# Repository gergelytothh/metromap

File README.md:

# Metromap

A map of the Budapest metro, designed to show trains moving on all four lines. There are 96 LEDs on the map: two at each station (one per direction) and one at each terminus. They are hand-wired and soldered onto the map and driven by an ESP32 through a custom PCB. Right now it runs a simulated train animation; live data from BKK is the next step.

I'd seen lit-up metro maps of other cities online, but none of Budapest, and I didn't like the design of the ones I found. Since I'm studying electrical engineering anyway, I decided to build my own.

## How it works

The LEDs are driven by two MAX7219 chips, controlled by an ESP32. Each chip has 16 outputs: 8 DIG (digit) pins that sink current and 8 SEG (segment) pins that source it. Each LED sits where one DIG line and one SEG line cross, so one chip can control 64 LEDs and the two together 128.

Only one DIG line is active at a time. The chip sets the SEG lines for the LEDs that should be lit in that row, pulls the DIG line low, then moves on to the next row. It cycles through all 8 rows hundreds of times a second, so every lit LED looks constantly on.

The two chips are daisy-chained: they share the ESP32's clock and load pins, and U1's data output feeds U2's data input. The ESP32 shifts out 32 bits, a 16-bit word for each chip (an 8-bit register address and 8 bits of data, which set the SEG lines for one DIG row), and then a pulse on LOAD makes both chips apply them at the same time.

There are 96 LEDs, so one chip wasn't enough. I split them by metro line, so each line stays on a single chip and both chips stay under the 64-LED limit:

| Chip | Lines | LEDs used | Spare slots |
|---|---|---|---|
| U1 | M1 + M2 | 40 | 24 |
| U2 | M3 + M4 | 56 | 8 |

Every LED has an ID (1–96) and is assigned a chip, a DIG and a SEG. This mapping table is in [station_map.h](firmware/metromap/station_map.h) (also as [a CSV](hardware/led-mapping.csv)).

The firmware builds on this table:

- **One LED by ID**: looks the ID up in the table and turns on that chip/DIG/SEG.
- **Walk test**: lights every LED in turn, 1 to 96, and prints its station to the Serial Monitor, so wiring mistakes are easy to spot.
- **Train mode**: each line gets a route, from one terminus out along the forward LEDs and back along the backward ones, and four trains, one per line, move one stop at a time.

## Hardware

I designed the driver PCB myself in KiCAD and had it made by NYÁKÁRUHÁZ Kft. It holds both MAX7219s in DIP sockets, so the soldering heat couldn't damage the chips. Every DIG and SEG pin goes to a labelled pad.

From each pad, a wire runs to the back of the map, where it connects to the right LEDs. That's around ~280 solder joints in total, all by hand.

*The back of the map. Every wire is labelled in pencil with its DIG/SEG line.*

| Part | What |
|---|---|
| Microcontroller | ESP32-WROOM-32U dev board |
| LED drivers | 2 × MAX7219 (DIP-24, socketed) |
| PCB | Own design in KiCAD, made by NYÁKÁRUHÁZ Kft. |
| LEDs | 96, one colour per line |
| Map | Printed poster on cardboard |
| Power | 5 V from USB, via the ESP32 |

Design files: [schematic (PDF)](hardware/Metromap%20schematic.pdf) · [KiCAD project](hardware/kicad/) · [3D render](docs/images/pcb-3d.png)

### What I'd do differently

- **The wiring.** It works, but it's hard to trace and service. Next time I'd group the LEDs on small boards or connectors behind each line, with ribbon cable to the driver board.
- **The ISET resistor.** Both chips share one 10 kΩ R1, but each MAX7219 should have its own. According to the datasheet’s output current curves, a shared resistor behaves roughly like 20 kΩ per chip, about 25 mA peak per segment instead of about 45 mA, and the split between the chips isn’t guaranteed to be even. It works and the brightness looks fine, but a second version would give each chip its own resistor.

## Build and flash

Built with Arduino IDE 2.3.10 and the Espressif ESP32 board package 3.3.12.

1. Install the **MD_MAX72xx** library (by majicDesigns, tested with 3.5.1) from the Library Manager.
2. Open `firmware/metromap/metromap.ino`.
3. Select **Tools → Board → ESP32 Dev Module** and the ESP32's serial port.
4. Upload.

Pick the mode in `loop()`: `trainMode()` runs the train animation, and `walkTest()` lights every LED in turn and prints each station to the Serial Monitor (115200 baud).

## What went wrong and how I fixed it

For a long time the addressing didn't work: telling the firmware to light a specific DIG/SEG lit the wrong LED. I lit one address at a time and wrote down which LED actually came on, until a pattern appeared: the MD_MAX72xx library numbers the columns in a different order from the chip's SEG pins. SEG_A is column 6, down to SEG_G at column 0, and only SEG_DP stays at column 7. I then tested that theory LED by LED, and it held. The fix is a single line in [metromap.ino](firmware/metromap/metromap.ino).

More in the [bring-up log](docs/bring-up-log.md), including how the datasheet corrected my assumption about the shared ISET resistor.

## What's next

- **Live trains.** I chose the ESP32 for its built-in Wi-Fi. The plan is to fetch data from BKK's open API using an API key. As it turns out, BKK doesn't publish live positions for metro trains, only a timetable that's updated in real time, so the map has to work out where each train is from that.
- **Turning a timetable into train positions.** This is the tricky part. Using the timetable directly, a train could disappear between two stations, or appear at several at once. Each train has to be tracked so that it's always shown at exactly one station: the last station it departed from, until its scheduled departure from the next one.

## Acknowledgements

The firmware and this README were developed in collaboration with Claude and Claude Code. The hardware design, PCB, wiring and testing are my own.

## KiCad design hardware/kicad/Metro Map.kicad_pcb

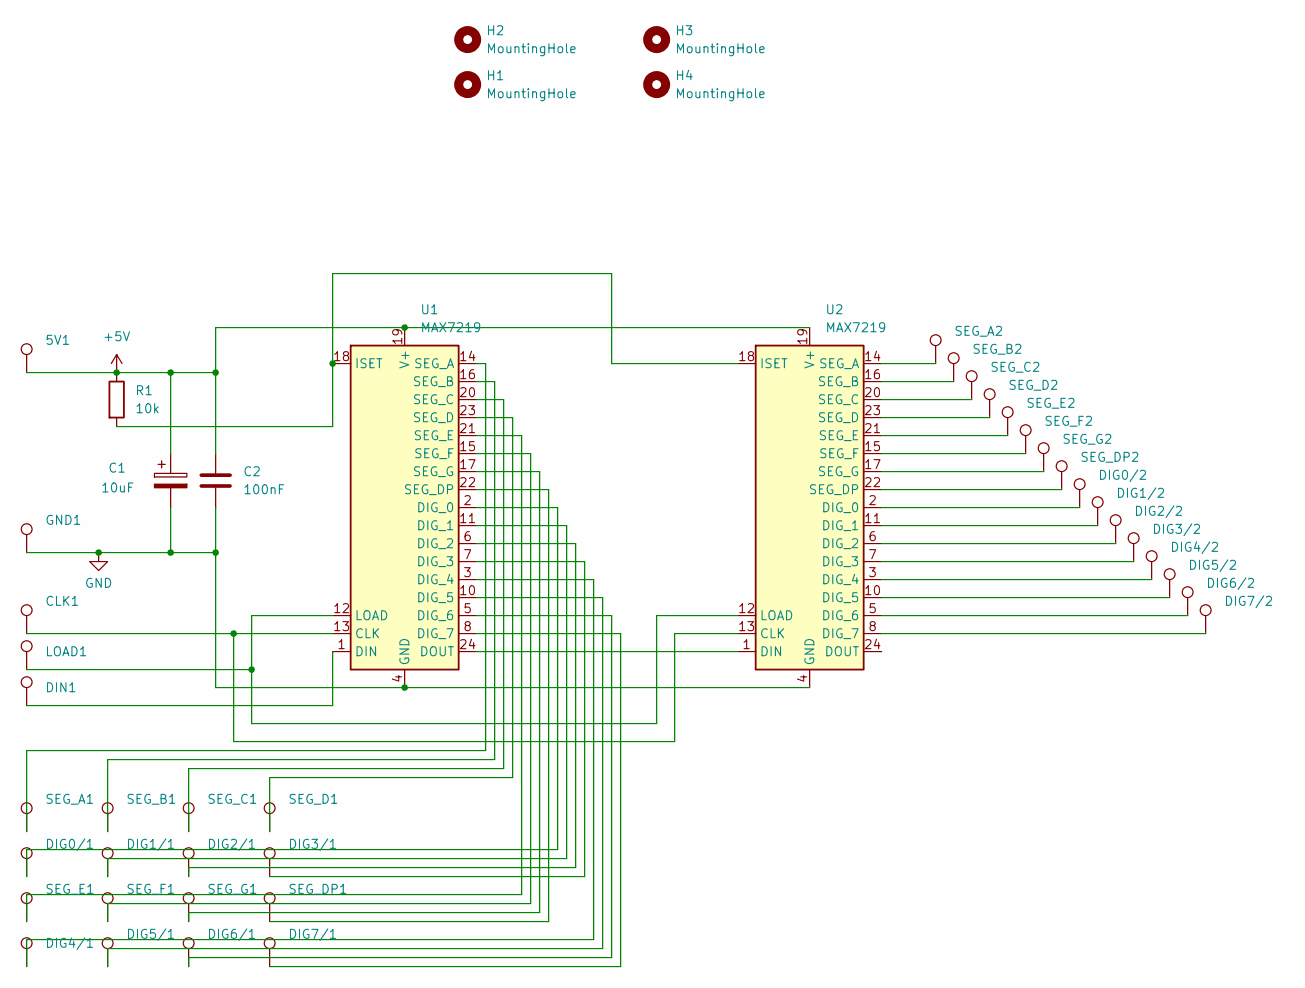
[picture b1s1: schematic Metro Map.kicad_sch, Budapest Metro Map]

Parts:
5V1: TestPoint_THTPad_D1.5mm_Drill0.7mm
C1: 10uF; CP_Radial_D5.0mm_P2.00mm
C2: 100nF; C_Disc_D5.0mm_W2.5mm_P2.50mm
CLK1: TestPoint_THTPad_D1.5mm_Drill0.7mm
DIG0/1, DIG0/2, DIG1/1, DIG1/2, DIG2/1, DIG2/2, DIG3/1, DIG3/2, DIG4/1, DIG4/2, DIG5/1, DIG5/2, DIG6/1, DIG6/2, DIG7/1, DIG7/2: TestPoint_THTPad_D1.5mm_Drill0.7mm
DIN1: TestPoint_THTPad_D1.5mm_Drill0.7mm
GND1: TestPoint_THTPad_D1.5mm_Drill0.7mm
H1, H2, H3, H4: MountingHole; MountingHole_3.2mm_M3
LOAD1: TestPoint_THTPad_D1.5mm_Drill0.7mm
R1: 10k; R_Axial_DIN0207_L6.3mm_D2.5mm_P7.62mm_Horizontal
SEG_A1, SEG_A2: TestPoint_THTPad_D1.5mm_Drill0.7mm
SEG_B1, SEG_B2: TestPoint_THTPad_D1.5mm_Drill0.7mm
SEG_C1, SEG_C2: TestPoint_THTPad_D1.5mm_Drill0.7mm
SEG_D1, SEG_D2: TestPoint_THTPad_D1.5mm_Drill0.7mm
SEG_DP1, SEG_DP2: TestPoint_THTPad_D1.5mm_Drill0.7mm
SEG_E1, SEG_E2: TestPoint_THTPad_D1.5mm_Drill0.7mm
SEG_F1, SEG_F2: TestPoint_THTPad_D1.5mm_Drill0.7mm
SEG_G1, SEG_G2: TestPoint_THTPad_D1.5mm_Drill0.7mm
U1, U2: MAX7219; DIP-24_W7.62mm

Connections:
+5V: 5V1.1, C1.1, C2.1, R1.1, U1.19 (V+), U2.19 (V+)
GND: C1.2, C2.2, GND1.1, U1.4 (GND), U1.9 (GND), U2.4 (GND), U2.9 (GND)
unnamed: CLK1.1, U1.13 (CLK), U2.13 (CLK)
unnamed: DIG0/1.1, U1.2 (DIG_0)
unnamed: DIG1/1.1, U1.11 (DIG_1)
unnamed: DIG2/1.1, U1.6 (DIG_2)
unnamed: DIG3/1.1, U1.7 (DIG_3)
unnamed: DIG4/1.1, U1.3 (DIG_4)
unnamed: DIG5/1.1, U1.10 (DIG_5)
unnamed: DIG6/1.1, U1.5 (DIG_6)
unnamed: DIG7/1.1, U1.8 (DIG_7)
unnamed: DIN1.1, U1.1 (DIN)
unnamed: U1.24 (DOUT), U2.1 (DIN)
unnamed: R1.2, U1.18 (ISET), U2.18 (ISET)
unnamed: LOAD1.1, U1.12 (LOAD), U2.12 (LOAD)
unnamed: SEG_A1.1, U1.14 (SEG_A)
unnamed: SEG_B1.1, U1.16 (SEG_B)
unnamed: SEG_C1.1, U1.20 (SEG_C)
unnamed: SEG_D1.1, U1.23 (SEG_D)
unnamed: SEG_DP1.1, U1.22 (SEG_DP)
unnamed: SEG_E1.1, U1.21 (SEG_E)
unnamed: SEG_F1.1, U1.15 (SEG_F)
unnamed: SEG_G1.1, U1.17 (SEG_G)
unnamed: DIG0/2.1, U2.2 (DIG_0)
unnamed: DIG1/2.1, U2.11 (DIG_1)
unnamed: DIG2/2.1, U2.6 (DIG_2)
unnamed: DIG3/2.1, U2.7 (DIG_3)
unnamed: DIG4/2.1, U2.3 (DIG_4)
unnamed: DIG5/2.1, U2.10 (DIG_5)
unnamed: DIG6/2.1, U2.5 (DIG_6)
unnamed: DIG7/2.1, U2.8 (DIG_7)
unnamed: SEG_A2.1, U2.14 (SEG_A)
unnamed: SEG_B2.1, U2.16 (SEG_B)
unnamed: SEG_C2.1, U2.20 (SEG_C)
unnamed: SEG_D2.1, U2.23 (SEG_D)
unnamed: SEG_DP2.1, U2.22 (SEG_DP)
unnamed: SEG_E2.1, U2.21 (SEG_E)
unnamed: SEG_F2.1, U2.15 (SEG_F)
unnamed: SEG_G2.1, U2.17 (SEG_G)

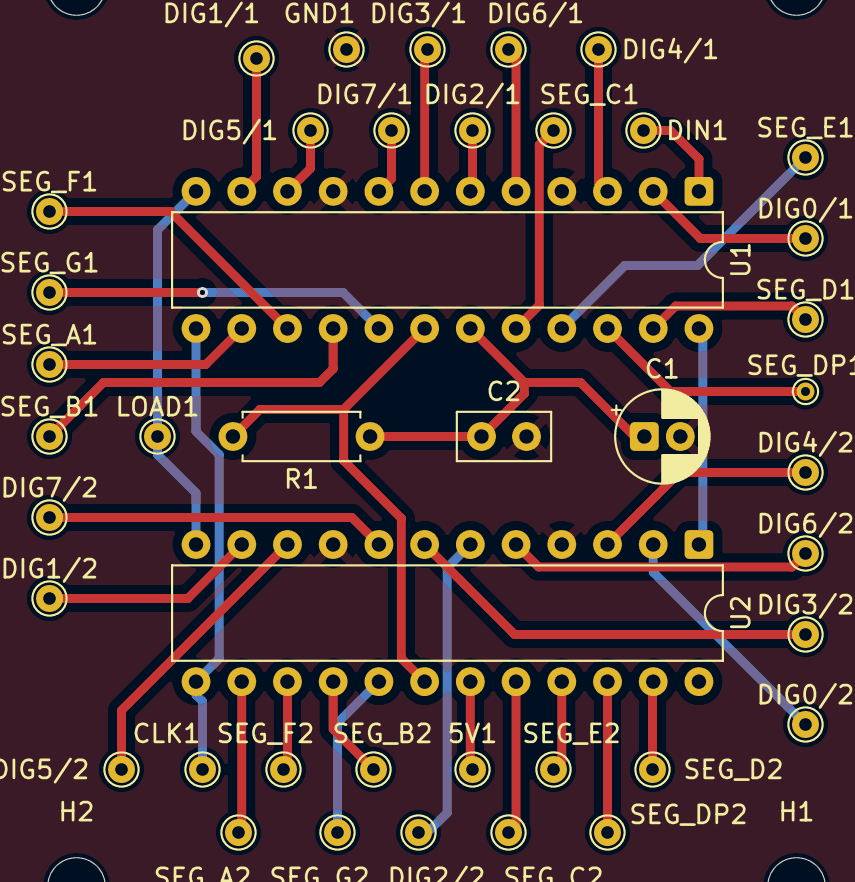
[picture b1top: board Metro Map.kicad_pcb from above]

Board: 2 copper layers, 46 parts (0 on the bottom side), 39 nets.
